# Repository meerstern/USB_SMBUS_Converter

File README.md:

# USB_SMBUS_Converter
USB SMBus converter with CP2112

## 概要 
  * [CP2112][1]を使用したUSB-SMBUS/I2C変換基板です  
  * [Simplicity Studio][2]を使用してVIDやPID等のパラメータを設定変更できます  
  * [USBオーディオブリッジ CP2615][3]のパラメータ書き換えに最適です  
  * サイズ30mm x20mm 

## 注意
 * [Simplicity Studio][2]を使用したパラメータ書き換えはOne-Time Programmable ROMで1回のみです  
 * 2回以上の書き換えはできませんので書き換えの際は間違えないように注意してください  
 * 出荷時の初期値は下記のパラメータ設定となっており、1回のみ別の値に書き換えできます  
 
|  Name  |  Default Value  |
| ---- | ---- |
|  VID  |  10C4h  |
|  PID  |  EA90h  |
|  Power Descriptor1  |  80h (Bus-Powered)  |
|  Power Descriptor2  |  32h (100 mA)  |
|  Release Number  |  0100h (Release Version 01.00)  |
|  Manufacturer String  |  Silicon Laboratories  |
|  Product Description String  |  CP2112 HID USB-to-SMBus Bridge  |
|  Serial String  |  Unique 8-character ASCII string |  

## 販売サイト
  * [スイッチサイエンス][4]
 
[1]: https://jp.silabs.com/interface/usb-bridges/classic/device.cp2112
[2]: https://jp.silabs.com/products/development-tools/software/simplicity-studio
[3]: https://github.com/meerstern/USB_PDM_Converter
[4]: https://www.switch-science.com/products/6489

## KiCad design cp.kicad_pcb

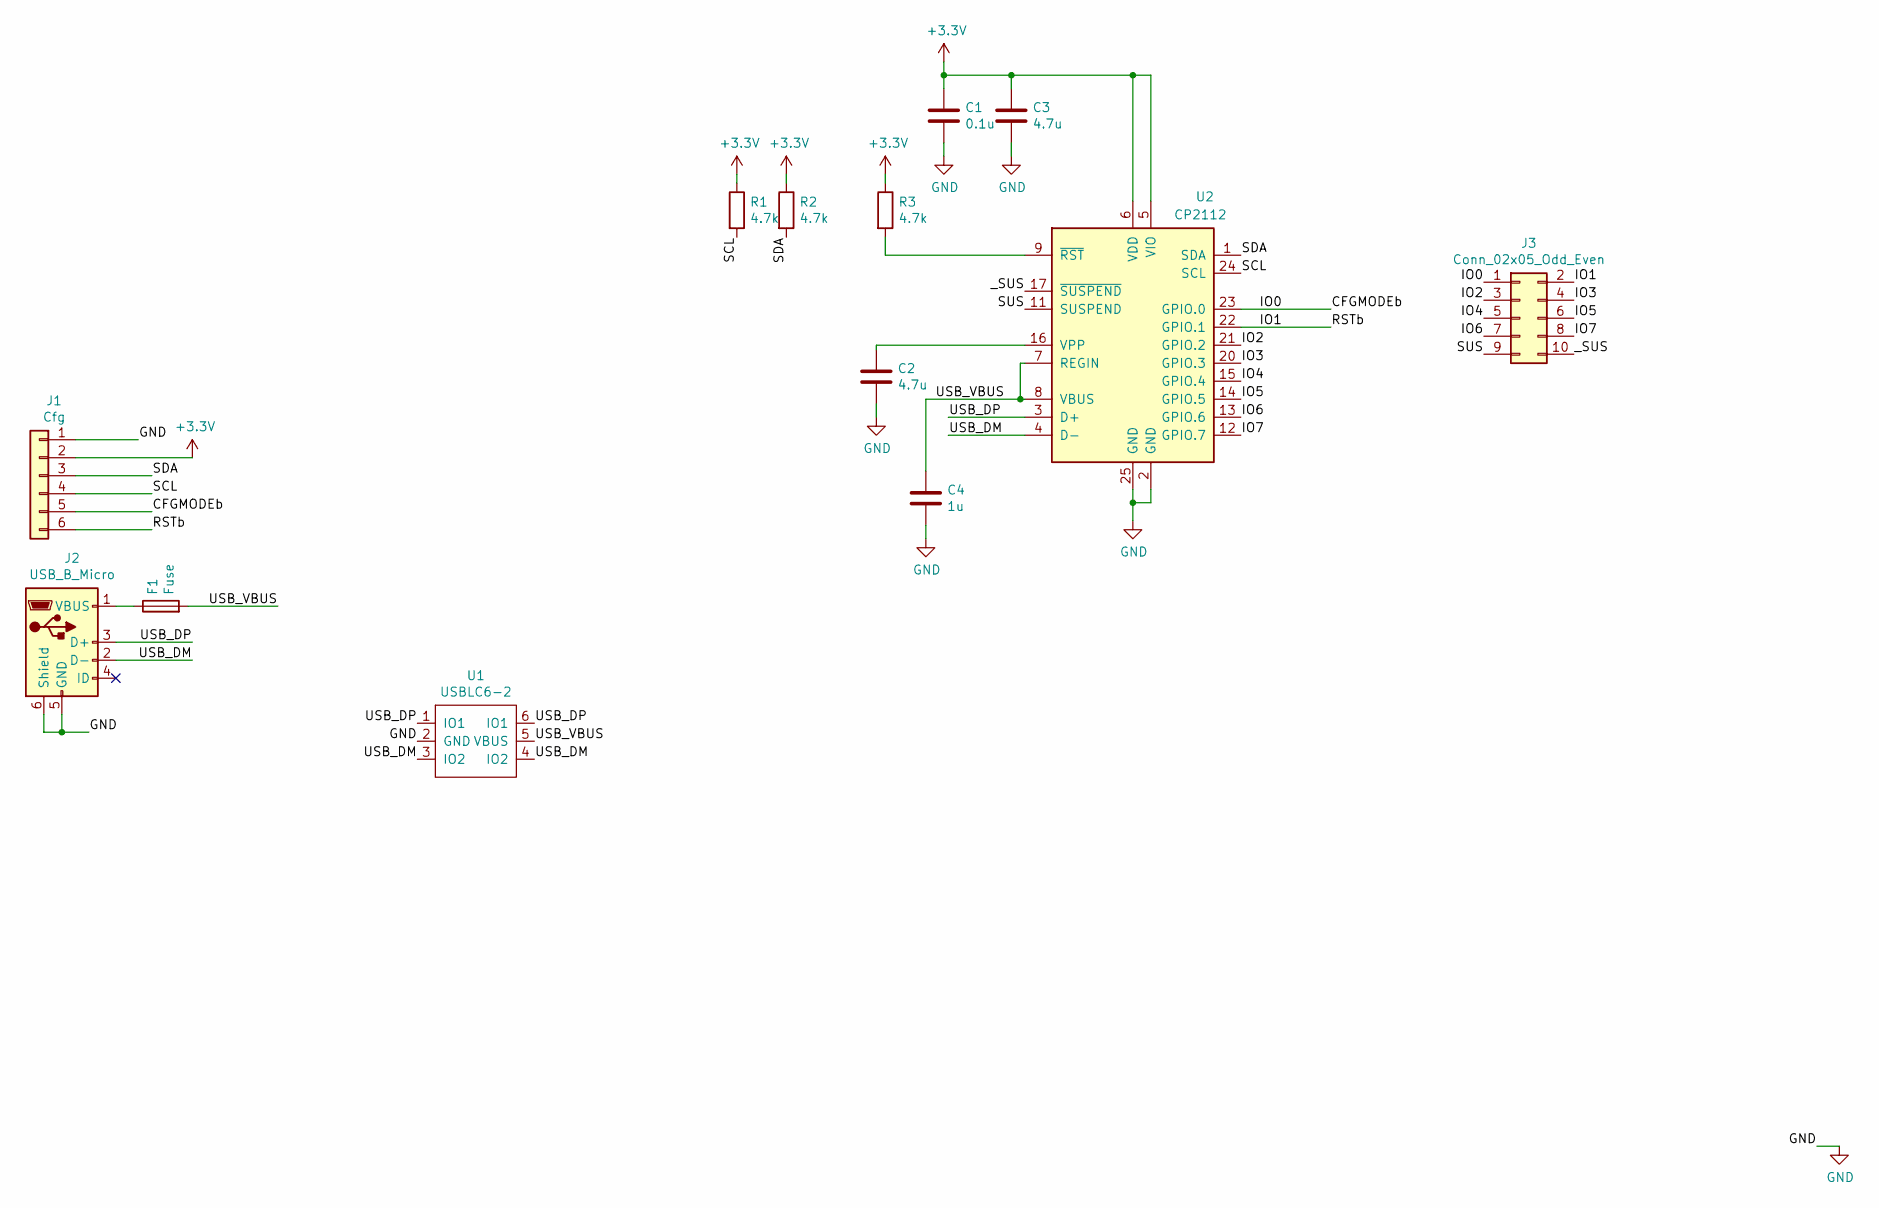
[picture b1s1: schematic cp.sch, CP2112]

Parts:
C1: 0.1u; C_0603_1608Metric
C2, C3: 4.7u; C_0805_2012Metric
C4: 1u; C_0603_1608Metric
F1: Fuse; Fuse_0603_1608Metric
J1: Cfg; PinHeader_1x06_P2.54mm_Vertical
J2: USB_B_Micro; CONN-10118194-0001LF-FCI
J3: Conn_02x05_Odd_Even; PinHeader_2x05_P2.54mm_Vertical
R1, R2, R3: 4.7k; R_0603_1608Metric
U1: USBLC6-2; SOT-23-6
U2: CP2112; QFN-24-1EP_4x4mm_P0.5mm_EP2.6x2.6mm

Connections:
+3V3: C1.1, C3.1, J1.2, R1.1, R2.1, R3.1, U2.5 (VIO), U2.6 (VDD)
/CFGMODEb: J1.5, J3.1, U2.23 (GPIO.0)
/IO1: J1.6, J3.2, U2.22 (GPIO.1)
/IO2: J3.3, U2.21 (GPIO.2)
/IO3: J3.4, U2.20 (GPIO.3)
/IO4: J3.5, U2.15 (GPIO.4)
/IO5: J3.6, U2.14 (GPIO.5)
/IO6: J3.7, U2.13 (GPIO.6)
/IO7: J3.8, U2.12 (GPIO.7)
/SCL: J1.4, R1.2, U2.24 (SCL)
/SDA: J1.3, R2.2, U2.1 (SDA)
/SUS: J3.9, U2.11 (SUSPEND)
/USB_DM: J2.2 (D-), U1.3 (IO2), U1.4 (IO2), U2.4 (D-)
/USB_DP: J2.3 (D+), U1.1 (IO1), U1.6 (IO1), U2.3 (D+)
/USB_VBUS: C4.1, F1.2, U1.5 (VBUS), U2.7 (REGIN), U2.8 (VBUS)
/_SUS: J3.10, U2.17 (~SUSPEND)
GND: C1.2, C2.2, C3.2, C4.2, J1.1, J2.5 (GND), J2.6 (Shield), U1.2 (GND), U2.2 (GND), U2.25 (GND)
unnamed: C2.1, U2.16 (VPP)
unnamed: F1.1, J2.1 (VBUS)
unnamed: R3.2, U2.9 (~RST)

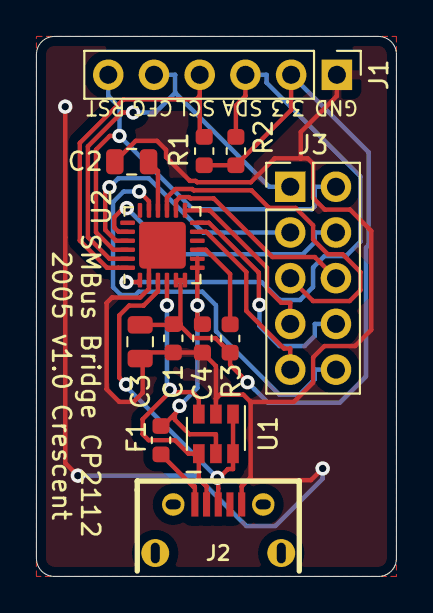
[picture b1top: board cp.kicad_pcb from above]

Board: 2 copper layers, 20.0 x 30.0 mm, 13 parts (0 on the bottom side), 20 nets.

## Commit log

2020-06-07 Add pcb data
2020-07-04 Add img files
2022-12-06 Add shop link
